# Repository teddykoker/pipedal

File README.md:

# Web Interfaced Pedal

## Quickstart

Plug pedal into 9V DC power supply, input, and output cables (like most guitar pedals).

Wait approximately 15 seconds, and then search for the Wifi Network “Pedal” on your computer. Open your web browser and open [http://pedal.local](http://pedal.local) if on Mac, otherwise open [http://192.168.4.1](http://192.168.4.1). The pedal can now be controlled via the web interface.

## Goal

The goal of this project was to create an electric guitar pedal that had the ability to be wirelessly controlled from any browser, by means of a local wifi connection. We had arbitrarily chose the ‘fuzz’ type pedal due to it’s analog simplicity (two high gain transistors). What follows is a brief report on the methodologies and results.

# Documentation

## Software

The pedal acts as a wireless access point allowing anyone nearby to connect to it from their network preferences. There is also a web server running on the pedal, which controls the pedal via two digital potentiometers connected to the GPIO pins of the embedded Raspberry Pi.

### Server

The server is written in Python using the [Tornado](http://www.tornadoweb.org/) web framework. This allows for fast and asyncronous websocket connects for low-latency controls. The websocket handler uses [spidev](https://github.com/doceme/py-spidev) to control the digitpots through an SPI interface, and [RPi.GPIO](https://sourceforge.net/projects/raspberry-gpio-python/) to control the relay.

### Frontend

The frontend of the website uses [Vue.js](https://vuejs.org/) to dynamically display and update the pedal controls.

### Installing Software on a New Raspberry Pi Zero

The board used for this project is a Raspberry Pi Zero W. Download the latest [Raspbian Lite Image](https://downloads.raspberrypi.org/raspbian_lite_latest) and flash it to your SD card. I recommend using [Etcher](https://www.balena.io/etcher/). Before ejecting the SD card, navigate to the SD card filesystem and do the following: Edit **config.txt** and append dtoverlay=dwc2 to the end of the file. Edit **cmdline.txt** and add modules-load=dwc2,g_serial after root separated by a single space on either side. Finally create a file called **ssh** (no extension) in the same directory.

Plug the Raspberry Pi into your computer via the center micro-USB connector. After waiting a few moments for the Pi to boot, you will be able to connect to the Pi as an ethernet device in your network settings. You can now ssh to the Pi with the following command: ssh pi@raspberry.local. The password will be “raspberry.” Now that you have a shell open, you can proceed to configuring the Access Point.

#### Configuring the Access Point

Update system:

```shell
sudo apt update && sudo apt upgrade
```

Install software:

```shell
sudo apt install dnsmasq hostapd
sudo systemctl stop dnsmasq
sudo systemctl stop hostapd
sudo reboot
```

_Note: the system will reboot so you will have reconnect to it like before._

Configure static IP:

```shell
sudo nano /etc/dhcpcd.conf
```

_Edit file so it looks like:_

```
interface wlan0
    static ip_address=192.168.4.1/24
    nohook wpa_supplicant
```

Restart dhcpcd:

```shell
sudo service dhcpcd restart
```

Backup and edit dnsmasq config:

```shell
sudo mv /etc/dnsmasq.conf /etc/dnsmasq.conf.orig

sudo nano /etc/dnsmasq.conf
```

_Add the following:_

```
interface=wlan0      # Use the wireless interface - usually wlan0
  dhcp-range=192.168.4.2,192.168.4.20,255.255.255.0,24h
```

Configure hostapd:

```shell
sudo nano /etc/hostapd/hostapd.conf
```

_Add the following:_

```
interface=wlan0
driver=nl80211
ssid=Pedal
channel=7
```

Then:

```shell
sudo nano /etc/default/hostapd
```

Replace:

```
DAEMON_CONF="/etc/hostapd/hostapd.conf"
```

Edit kernel parameters:

```shell
sudo nano /etc/sysctl.conf
```

Uncomment this line:

```
net.ipv4.ip_forward=1
```

Add a masquerade for outbound traffic on eth0:

```shell
sudo iptables -t nat -A  POSTROUTING -o eth0 -j MASQUERADE
```

Save the iptables rule:

```shell
sudo sh -c "iptables-save > /etc/iptables.ipv4.nat"
```

Edit /etc/rc.local:

```shell
sudo nano /etc/rc.local
```

Add this just above "exit 0" to install these rules on boot:

```shell
iptables-restore < /etc/iptables.ipv4.nat
```

#### Install the Pi-Pedal software

Install git and pip:

```shell
sudo apt install git python-pip
```

Clone the pi-pedal code from my repository:

```shell
git clone https://github.com/teddykoker/pipedal
```

Install requirements:

```shell
sudo pip install -r pipedal/requirements.txt
```

Edit /etc/rc.local:

```shell
sudo nano /etc/rc.local
```

Add this just above "exit 0" to run on boot:

```
/home/pi/pipedal/pedal.py
```

Edit hostname:

```shell
sudo nano /etc/hostname
```

Replace name with `pedal`

## Hardware

### Schematic

A 9v linear regulator (LT 7805) can be seen on the top left of the schematic, with the relay system on the middle left, and digital MOSFET toggle control on the bottom left. On the right of the schematic is the necessary analog circuitry to produce the fuzz effect, with all of the connectors that will be required on the PCB, to connect to the Raspberry Pi inside the enclosure. The fuzz circuitry is based around the two high gain (BC548 transistors).

### Version 1: Breadboard

The breadboard circuitry follows directly from the general schematic. Just to point out key components for quick reference - the relay is in orange, the manually latching pedal switch is on the bottom right, the two audio connectors are on the top right. The blue breakout board is to connect the Raspberry’s male header pins to the breadboard. The two DIP8 ICs on the left breadboard are the digital potentiometers controlled by the raspberry pi. The one on the top controls volume, and the one on the bottom controls the fuzz saturation. Both are interfaced to the RasPi via SPI.On the bottom left you can see two bigger (47u) audio capacitors and a heatsinked linear regulator to produce a 5v rail from the 9v wall adapter. There is an issue with this power supply however. This specific variant of 7805 IC apparently cannot handle the current needed by the Raspberry Pi on bootup, and the 5v rail wiggles as the UVLO circuitry of the raspberry pi starts and stops. The PCB mentioned later does not have this problem for whatever reason.

#### Issues with Schematic

1. Connection from ON-OFF to the RasPi must be done with a 10K ohm resistor - not directly.
2. The 9v connector is technically backwards in the PCB schematic - the footprint has to be reversed.

### Version 2: PCB and Enclosure

The PCB was designed from the same exact schematic as the breadboard was built from. The software used was the free and open source KiCAD, from EDA. The manufacturer of the PCB was OSHPark, a U.S. based rapid-prototyping company.

#### Issues with PCB variant

The fuzz circuitry isn’t working at all in the new PCB. There is absolutely no coupling of any sound through the fuzz circuitry. Everything else works though - after heavy modification. The relay is able to flip from wireless control using the RasPi, and the audio-pass functionality (when the pedal is off) passes the audio to the output undisturbed. One the pedal is turned on, and fuzz is supposed to be applied, no audio is passed through, denoting an issue with just the fuzz circuitry. Keep in mind that these issues are only with the PCB variant, not with the breadboard variant. The breadboard completely works except for the overcurrenting of the 7805 regulator.

# Next Steps

1. Hardware fixes:
   1. Correct reversal of 9v barrel jack footprint
   2. Add in 10 kOhm resistor
   3. Properly diagnose the 5v linear regulator, and completely understand why is wasn’t working on the breadboard - so we could better prevent this issue in the future - even though it worked on the PCB.
   4. Properly electrically test the fuzz circuitry with a function generator and an oscilloscope (there are direct FUZZ_IN and FUZZ_OUT male headers on the board for diagnosis) and determine what the mode of failure is.
2. Allow saving/restoring of guitar pedal settings
3. Add more effects

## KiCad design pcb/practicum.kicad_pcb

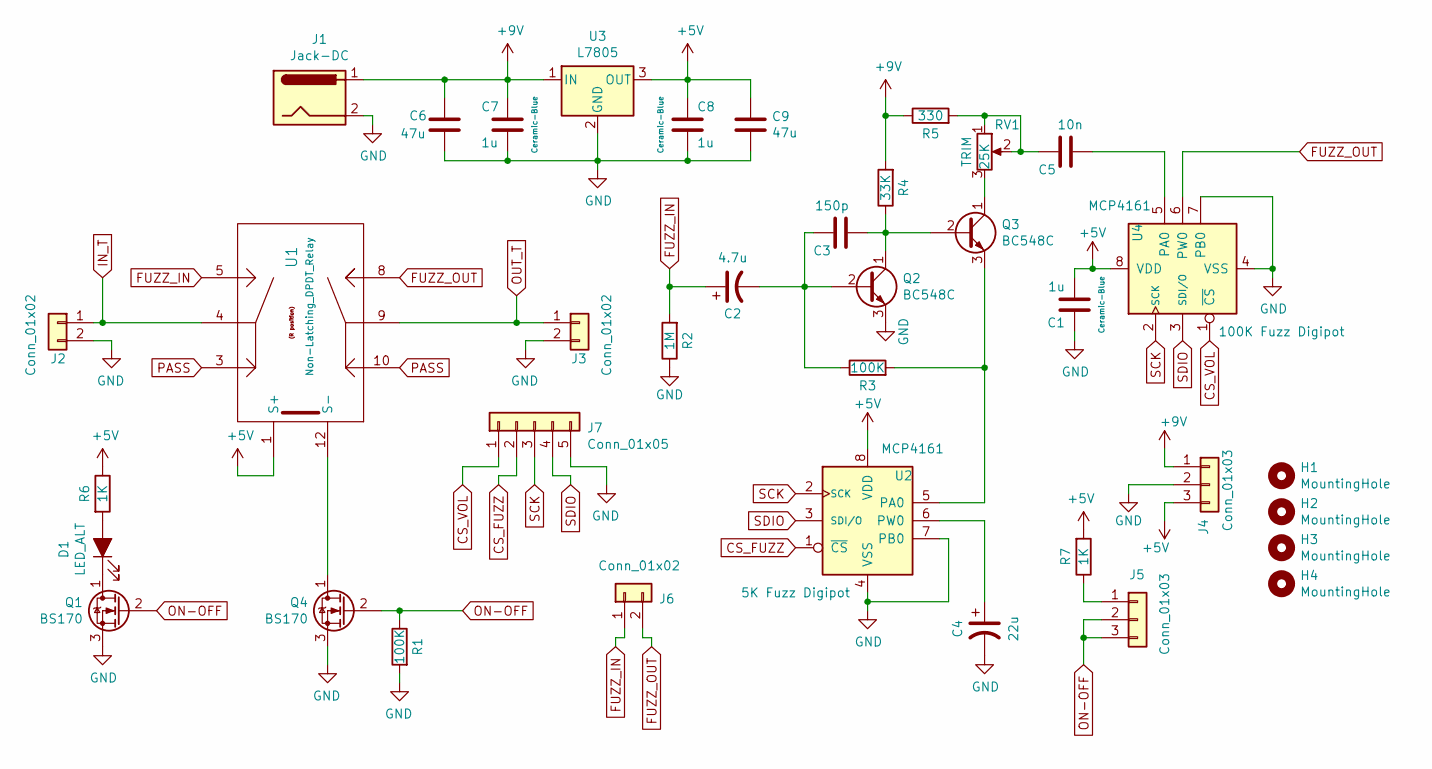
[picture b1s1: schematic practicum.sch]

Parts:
C1, C7, C8: 1u; C_Disc_D4.3mm_W1.9mm_P5.00mm
C2: 4.7u; CP_Radial_D5.0mm_P2.50mm
C3: 150p; C_Disc_D4.3mm_W1.9mm_P5.00mm
C4: 22u; CP_Radial_D6.3mm_P2.50mm
C5: 10n; C_Disc_D3.0mm_W1.6mm_P2.50mm
C6, C9: 47u; CP_Radial_D8.0mm_P2.50mm
D1: LED_ALT; PinHeader_1x02_P2.54mm_Vertical
H1, H2, H3, H4: MountingHole; MountingHole_2.2mm_M2_Pad_Via
J1: Jack-DC; BarrelJack_Horizontal
J2, J3, J6: Conn_01x02; PinHeader_1x02_P2.54mm_Vertical
J4, J5: Conn_01x03; PinHeader_1x03_P2.54mm_Vertical
J7: Conn_01x05; PinHeader_1x05_P2.54mm_Vertical
Q1, Q4: BS170; TO-92_Inline_Wide
Q2, Q3: BC548C; TO-92_Inline_Wide
R1, R3: 100K; R_Axial_DIN0207_L6.3mm_D2.5mm_P7.62mm_Horizontal
R2: 1M; R_Axial_DIN0207_L6.3mm_D2.5mm_P7.62mm_Horizontal
R4: 33K; R_Axial_DIN0207_L6.3mm_D2.5mm_P7.62mm_Horizontal
R5: 330; R_Axial_DIN0207_L6.3mm_D2.5mm_P7.62mm_Horizontal
R6, R7: 1K; R_Axial_DIN0207_L6.3mm_D2.5mm_P7.62mm_Horizontal
RV1: 25K; 3362P
U1: Non-Latching_DPDT_Relay; EC2-5NU_KEMET_Relay
U2, U4: MCP4161; DIP-8_W7.62mm
U3: L7805; TO-220-3_Vertical

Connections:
+5V: C1.2, C8.1, C9.1, J4.3, R6.1, R7.2, U1.1 (S+), U2.8 (VDD), U3.3 (OUT), U4.8 (VDD)
+9V: C6.1, C7.1, J1.1, J4.1, R4.2, R5.1, U3.1 (IN)
CS_FUZZ: J7.2, U2.1 (~CS)
CS_VOL: J7.1, U4.1 (~CS)
FUZZ_IN: C2.1, J6.1, R2.2, U1.5
FUZZ_OUT: J6.2, U1.8, U4.6 (PW0)
GND: C1.1, C4.2, C6.2, C7.2, C8.2, C9.2, J1.2, J2.2, J3.2, J4.2, J7.5, Q1.3 (S), Q2.3 (E), Q4.3 (S), R1.2, R2.1, U2.4 (VSS), U2.7 (PB0), U3.2 (GND), U4.4 (VSS), U4.7 (PB0)
IN_T: J2.1, U1.4
unnamed: C2.2, C3.1, Q2.2 (B), R3.1
unnamed: C3.2, Q2.1 (C), Q3.2 (B), R4.1
unnamed: C4.1, U2.6 (PW0)
unnamed: C5.1, R5.2, RV1.1, RV1.2
unnamed: C5.2, U4.5 (PA0)
unnamed: D1.1 (K), Q1.1 (D)
unnamed: D1.2 (A), R6.2
unnamed: J5.1, R7.1
unnamed: Q3.1 (C), RV1.3
unnamed: Q3.3 (E), R3.2, U2.5 (PA0)
unnamed: Q4.1 (D), U1.12 (S-)
ON-OFF: J5.2, J5.3, Q1.2 (G), Q4.2 (G), R1.1
OUT_T: J3.1, U1.9
PASS: U1.3, U1.10
SCK: J7.3, U2.2 (SCK), U4.2 (SCK)
SDIO: J7.4, U2.3 (SDI/O), U4.3 (SDI/O)

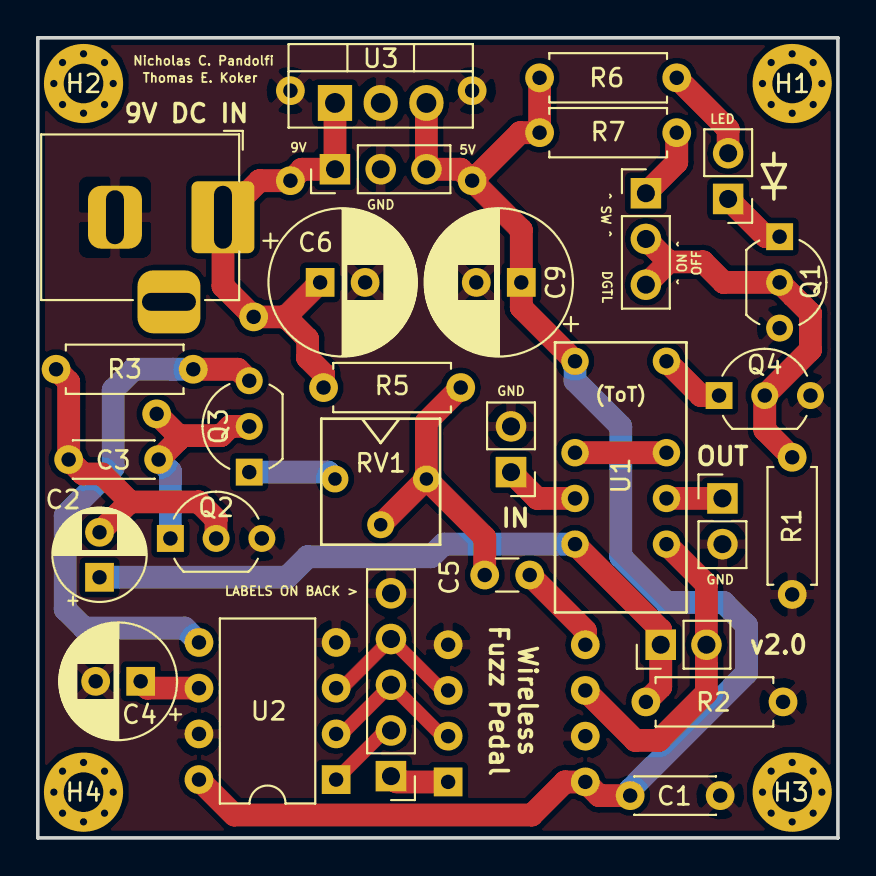
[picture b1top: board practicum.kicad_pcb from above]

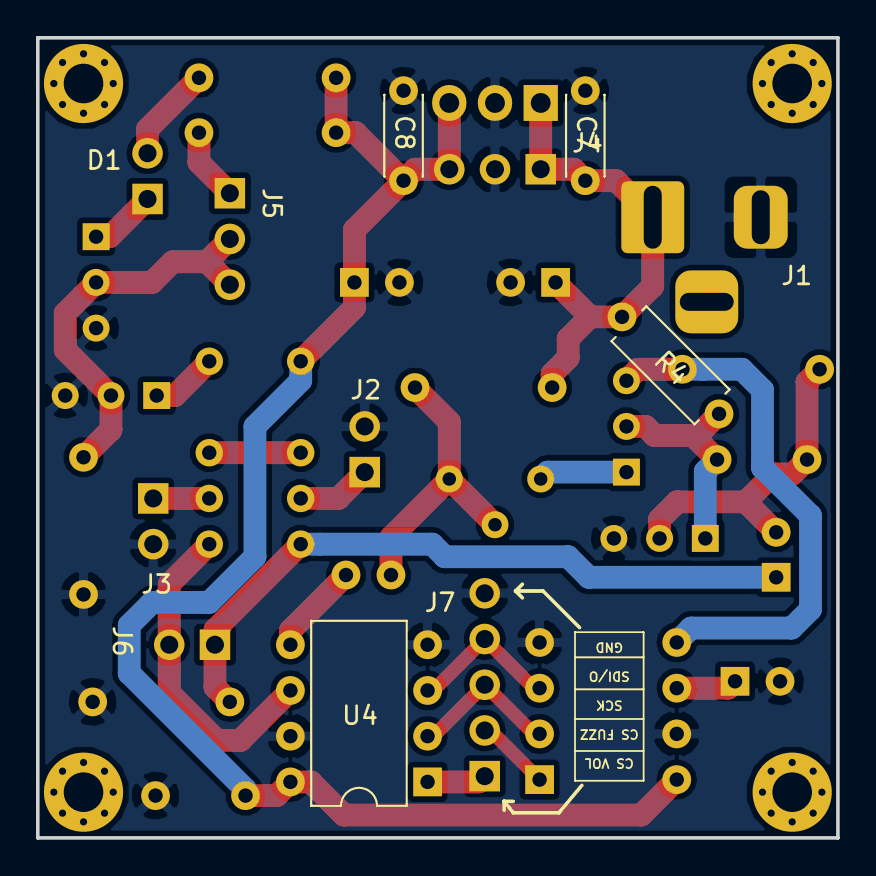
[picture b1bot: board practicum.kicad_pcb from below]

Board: 2 copper layers, 44.4 x 44.5 mm, 37 parts (4 on the bottom side), 24 nets.

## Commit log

2019-01-28 added files
2019-01-28 REadme
2019-01-28 asdf
2019-01-28 made executable
2019-01-29 adsf'
2019-01-29 Asdf"
2019-02-18 test
2019-02-18 float fix
2019-02-25 font stuff
2019-02-26 added pcb files
